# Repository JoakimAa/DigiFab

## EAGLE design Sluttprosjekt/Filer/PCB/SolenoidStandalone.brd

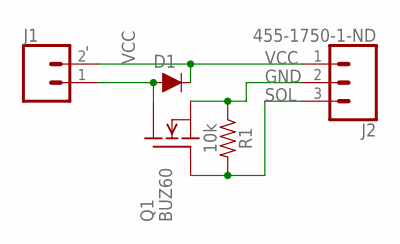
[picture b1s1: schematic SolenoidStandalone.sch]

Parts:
D1: 200mA/100V/1V; DIODE-1N4148
J1: CONN_02; 1X02
J2: 455-1750-1-ND; 1X03
Q1: BUZ60; TO220
R1: 10k; AXIAL-0.3

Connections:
-: D1.A, J1.1, Q1.2 (D)
GND: J2.2, Q1.3 (S), R1.P$1 (1)
SOL: J2.3, Q1.1 (G), R1.P$2 (2)
VCC: D1.C, J1.2, J2.1

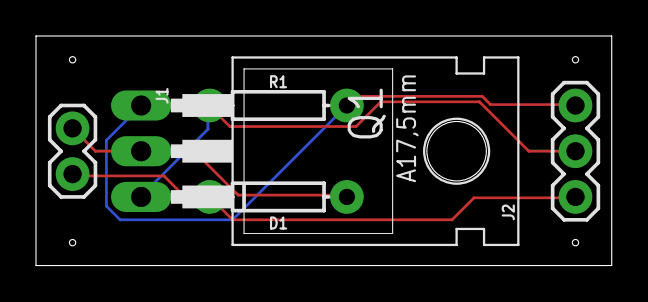
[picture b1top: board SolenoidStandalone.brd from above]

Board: 2 copper layers, 32.0 x 12.8 mm, 5 parts (0 on the bottom side), 4 nets.

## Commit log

2020-08-31 La til docs
2020-09-21 Added files to Oppgave 2
2020-09-21 Changed folder
2020-09-21 Fixed images
2020-09-23 Added fusion 360 iframe
2022-04-28 Added files
2022-04-28 Moved files to folders
2022-04-28 Added more files
2022-05-02 Added sluttprosjekt
2022-05-02 Added pictures
2022-05-02 Moved stuff
2022-05-02 Small change
2022-05-02 Small changes
2022-05-02 Changed iframe

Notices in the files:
parts and their libraries:
SparkFun-DiscreteSemi: Licensing: Creative Commons ShareAlike 4.0 International - https://creativecommons.org/licenses/by-sa/4.0
